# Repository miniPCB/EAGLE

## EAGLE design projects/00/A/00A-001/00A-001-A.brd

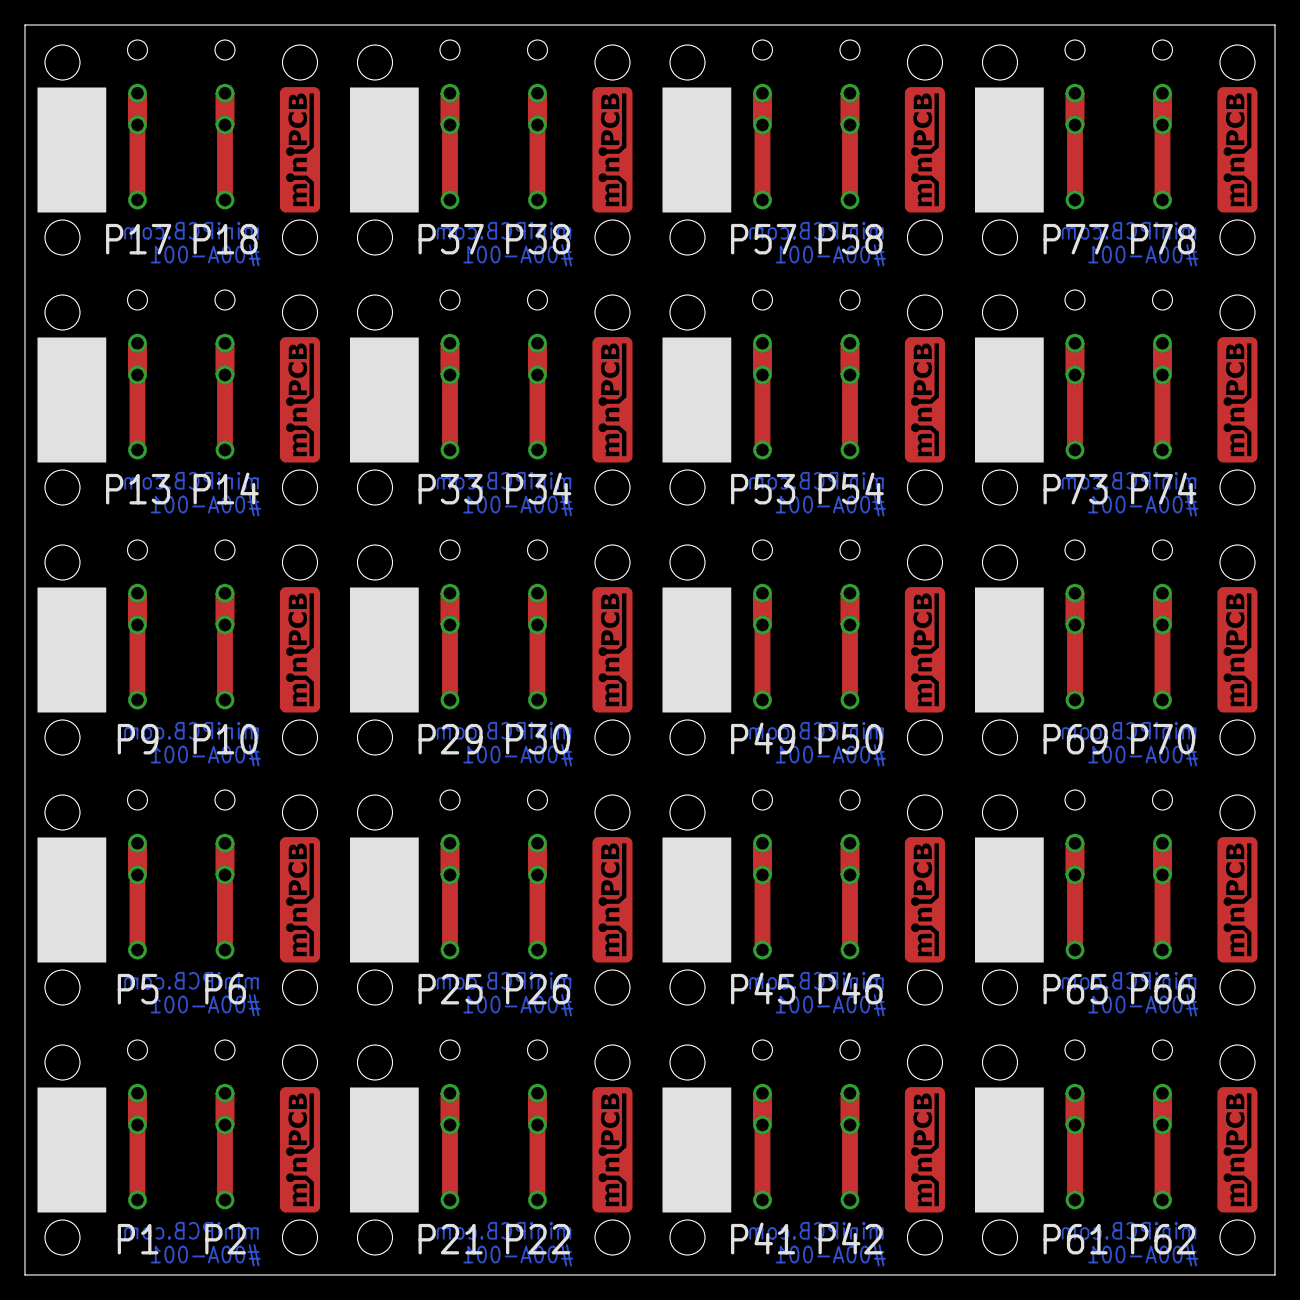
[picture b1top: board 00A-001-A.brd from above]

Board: 2 copper layers, 100.0 x 100.0 mm, 100 parts (0 on the bottom side), 40 nets.

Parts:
E$1, E$2, E$3, E$4, E$5, E$6, E$7, E$8, E$9, E$10, E$11, E$12, E$13, E$14, E$15, E$16, E$17, E$18, E$19, E$20: MINIPCB-LOGO
P1, P2, P5, P6, P9, P10, P13, P14, P17, P18, P21, P22, P25, P26, P29, P30, P33, P34, P37, P38, P41, P42, P45, P46, P49, P50, P53, P54, P57, P58, P61, P62, P65, P66, P69, P70, P73, P74, P77, P78: PINS_1_TESTPOINT_KE5000
P3, P4, P7, P8, P11, P12, P15, P16, P19, P20, P23, P24, P27, P28, P31, P32, P35, P36, P39, P40, P43, P44, P47, P48, P51, P52, P55, P56, P59, P60, P63, P64, P67, P68, P71, P72, P75, P76, P79, P80: PINS_1_1MM

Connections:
unnamed: P1.1, P3.1, P3.2
unnamed: P2.1, P4.1, P4.2
unnamed: P5.1, P7.1, P7.2
unnamed: P6.1, P8.1, P8.2
unnamed: P9.1, P11.1, P11.2
unnamed: P10.1, P12.1, P12.2
unnamed: P13.1, P15.1, P15.2
unnamed: P14.1, P16.1, P16.2
unnamed: P17.1, P19.1, P19.2
unnamed: P18.1, P20.1, P20.2
unnamed: P21.1, P23.1, P23.2
unnamed: P22.1, P24.1, P24.2
unnamed: P25.1, P27.1, P27.2
unnamed: P26.1, P28.1, P28.2
unnamed: P29.1, P31.1, P31.2
unnamed: P30.1, P32.1, P32.2
unnamed: P33.1, P35.1, P35.2
unnamed: P34.1, P36.1, P36.2
unnamed: P37.1, P39.1, P39.2
unnamed: P38.1, P40.1, P40.2
unnamed: P41.1, P43.1, P43.2
unnamed: P42.1, P44.1, P44.2
unnamed: P45.1, P47.1, P47.2
unnamed: P46.1, P48.1, P48.2
unnamed: P49.1, P51.1, P51.2
unnamed: P50.1, P52.1, P52.2
unnamed: P53.1, P55.1, P55.2
unnamed: P54.1, P56.1, P56.2
unnamed: P57.1, P59.1, P59.2
unnamed: P58.1, P60.1, P60.2
unnamed: P61.1, P63.1, P63.2
unnamed: P62.1, P64.1, P64.2
unnamed: P65.1, P67.1, P67.2
unnamed: P66.1, P68.1, P68.2
unnamed: P69.1, P71.1, P71.2
unnamed: P70.1, P72.1, P72.2
unnamed: P73.1, P75.1, P75.2
unnamed: P74.1, P76.1, P76.2
unnamed: P77.1, P79.1, P79.2
unnamed: P78.1, P80.1, P80.2

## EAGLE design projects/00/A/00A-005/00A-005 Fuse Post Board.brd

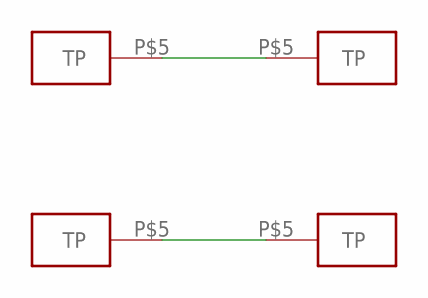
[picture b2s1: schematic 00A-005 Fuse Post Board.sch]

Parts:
U$1, U$2, U$3, U$4: TESTPOINT2M4; SCREW_TERMINAL_M4

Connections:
unnamed: U$1.P$5, U$3.P$5
unnamed: U$2.P$5, U$4.P$5

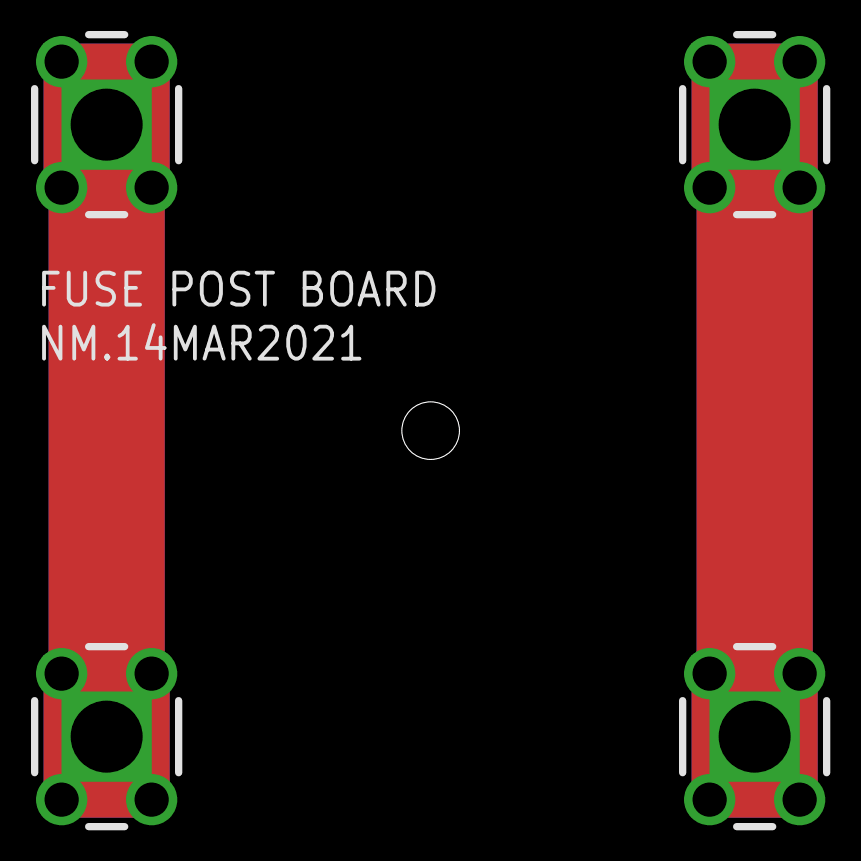
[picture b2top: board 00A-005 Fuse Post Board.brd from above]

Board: 2 copper layers, 4 parts (0 on the bottom side), 2 nets.

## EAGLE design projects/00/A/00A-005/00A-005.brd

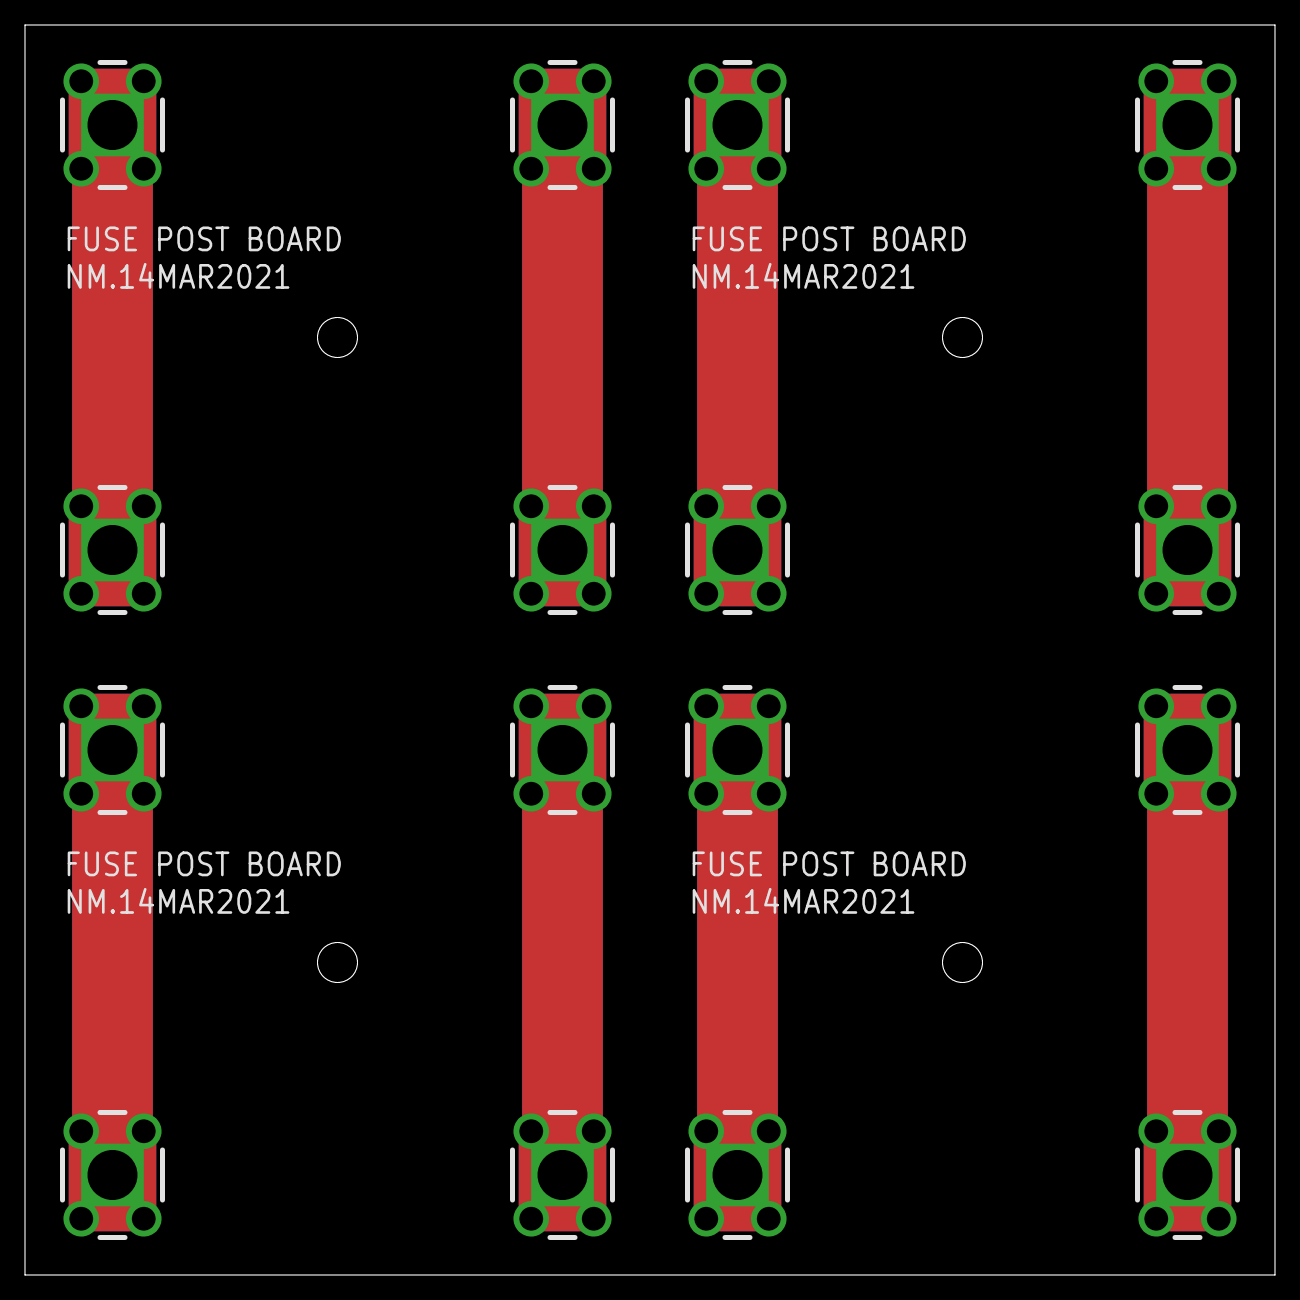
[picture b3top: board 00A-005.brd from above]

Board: 2 copper layers, 100.0 x 100.0 mm, 16 parts (0 on the bottom side), 8 nets.

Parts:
U$1, U$2, U$3, U$4, U$5, U$6, U$7, U$8, U$9, U$10, U$11, U$12, U$13, U$14, U$15, U$16: TESTPOINT2M4; SCREW_TERMINAL_M4

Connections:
unnamed: U$1.P$5, U$3.P$5
unnamed: U$2.P$5, U$4.P$5
unnamed: U$5.P$5, U$7.P$5
unnamed: U$6.P$5, U$8.P$5
unnamed: U$9.P$5, U$11.P$5
unnamed: U$10.P$5, U$12.P$5
unnamed: U$13.P$5, U$15.P$5
unnamed: U$14.P$5, U$16.P$5

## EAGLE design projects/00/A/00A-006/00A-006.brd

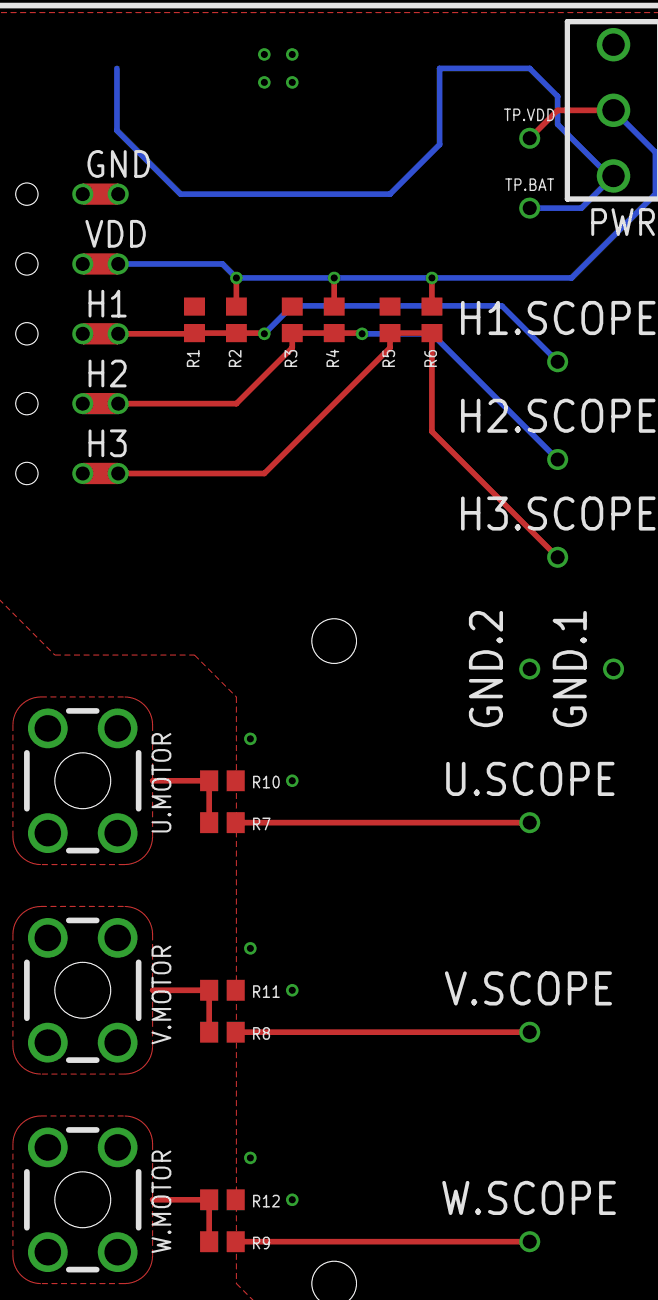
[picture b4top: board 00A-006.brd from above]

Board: 2 copper layers, 33 parts (1 on the bottom side), 12 nets.

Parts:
B1: CR3032; BATTERY-CR3032-KE3034
GND.1: PINS_1_TESTPOINT_KE5000
GND.2: TESTPOINTKE5000; PINS_1_TESTPOINT_KE5000
H1.SCOPE, H2.SCOPE, H3.SCOPE: PINS_1_TESTPOINT_KE5000
H1.SENSOR: H1; PINS_1_1MM
H2.SENSOR: H2; PINS_1_1MM
H3.SENSOR: H3; PINS_1_1MM
H.GND: GND; PINS_1_1MM
H.VDD: VDD; PINS_1_1MM
PWR: CK1101
R1, R2, R3, R4, R5, R6: 2k2; R0805
R7, R8, R9, R10, R11, R12: 220k; R0805
TP.BAT, TP.VDD: TESTPOINTKE5000-SMTEXT; PINS_1_TESTPOINT_KE5000_NOTEXT
U$1: MINIPCB_0P50X100; MINIPCB_0P_50X100
U.MOTOR: SCREW-TERMINAL-M3
U.SCOPE: PINS_1_TESTPOINT_KE5000
V.MOTOR: SCREW-TERMINAL-M3
V.SCOPE: PINS_1_TESTPOINT_KE5000
W.MOTOR: SCREW-TERMINAL-M3
W.SCOPE: PINS_1_TESTPOINT_KE5000

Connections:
GND: B1.3-, GND.1.1, GND.2.1, H.GND.1, H.GND.2, R1.1, R3.1, R5.1, R10.2, R11.2, R12.2
H1: H1.SCOPE.1, H1.SENSOR.1, H1.SENSOR.2, R1.2, R2.2
H2: H2.SCOPE.1, H2.SENSOR.1, H2.SENSOR.2, R3.2, R4.2
H3: H3.SCOPE.1, H3.SENSOR.1, H3.SENSOR.2, R5.2, R6.2
HVDD: H.VDD.1, H.VDD.2, PWR.P$2, R2.1, R4.1, R6.1, TP.VDD.1
U.MOTOR: R7.1, R10.1, U.MOTOR.1, U.MOTOR.2, U.MOTOR.3, U.MOTOR.4
U.SCOPE: R7.2, U.SCOPE.1
V.BAT: B1.1+, B1.2+, PWR.P$1, TP.BAT.1
V.MOTOR: R8.1, R11.1, V.MOTOR.1, V.MOTOR.2, V.MOTOR.3, V.MOTOR.4
V.SCOPE: R8.2, V.SCOPE.1
W.MOTOR: R9.1, R12.1, W.MOTOR.1, W.MOTOR.2, W.MOTOR.3, W.MOTOR.4
W.SCOPE: R9.2, W.SCOPE.1

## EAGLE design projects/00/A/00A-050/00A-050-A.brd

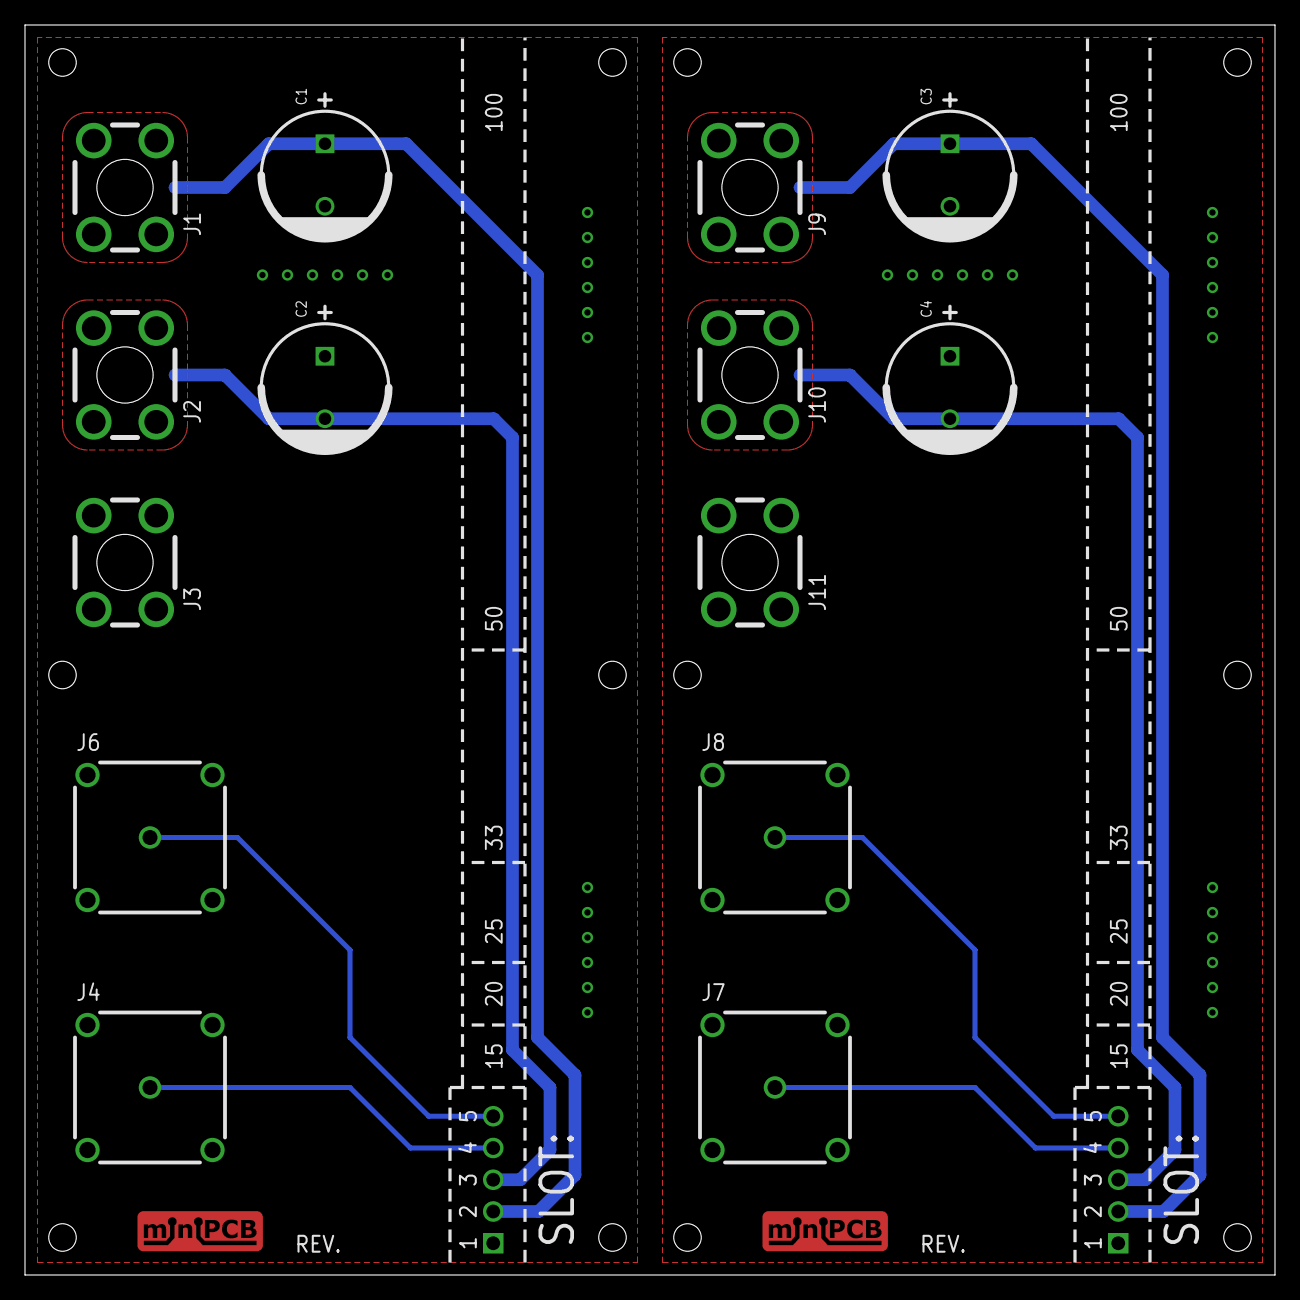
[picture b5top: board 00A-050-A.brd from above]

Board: 2 copper layers, 100.0 x 100.0 mm, 18 parts (0 on the bottom side), 10 nets.

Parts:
C1, C2, C3, C4: C5MM
J1, J9: +V; SCREW-TERMINAL-M3
J2, J10: -V; SCREW-TERMINAL-M3
J3, J11: GND; SCREW-TERMINAL-M3
J4, J7: IN.A; B35N14H
J5, J12: SLOT: A; MINIPCB_DOCK_5P
J6, J8: OUT.A; B35N14H
PCB, PCB1: MINIPCB_DOCK_50X100

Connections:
GND: C1.-, C2.+, J3.1, J3.2, J3.3, J3.4, J4.2.GND, J4.3.GND, J4.4.GND, J4.5.GND, J5.1, J6.2.GND, J6.3.GND, J6.4.GND, J6.5.GND
GND1: C3.-, C4.+, J7.2.GND, J7.3.GND, J7.4.GND, J7.5.GND, J8.2.GND, J8.3.GND, J8.4.GND, J8.5.GND, J11.1, J11.2, J11.3, J11.4, J12.1
unnamed: J4.1.SIG, J5.4
unnamed: J5.5, J6.1.SIG
unnamed: J7.1.SIG, J12.4
unnamed: J8.1.SIG, J12.5
V+: C1.+, J1.1, J1.2, J1.3, J1.4, J5.2
V+1: C3.+, J9.1, J9.2, J9.3, J9.4, J12.2
V-: C2.-, J2.1, J2.2, J2.3, J2.4, J5.3
V-1: C4.-, J10.1, J10.2, J10.3, J10.4, J12.3
